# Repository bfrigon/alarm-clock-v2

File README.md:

alarm-clock
===========

3D Model render:

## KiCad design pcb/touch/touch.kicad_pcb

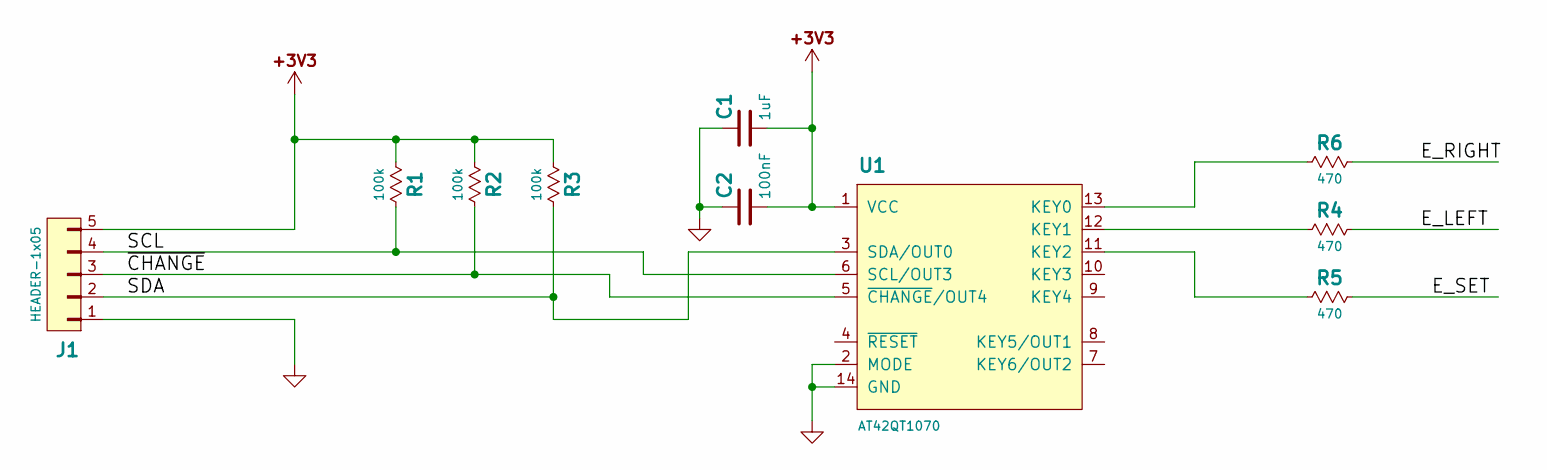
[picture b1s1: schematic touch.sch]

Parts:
C1: 1uF; C-0805
C2: 100nF; C-0603
J1: HEADER-1x05; WP-50mil-1x05
R1, R2, R3: 100k; C-0603
R4, R5, R6: 470; C-0603
U1: AT42QT1070; 14N

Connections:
+3V3: C1.1, C2.1, J1.5, R1.1, R2.1, R3.1, U1.1 (VCC)
/E_LEFT: R4.2
/E_RIGHT: R6.2
/E_SET: R5.2
/SCL: J1.4, R1.2, U1.6 (SCL/OUT3)
/SDA: J1.2, R3.2, U1.3 (SDA/OUT0)
/~CHANGE: J1.3, R2.2, U1.5 (~CHANGE~/OUT4)
GND: C1.2, C2.2, J1.1, U1.2 (MODE), U1.14 (GND)
unnamed: R4.1, U1.12 (KEY1)
unnamed: R5.1, U1.11 (KEY2)
unnamed: R6.1, U1.13 (KEY0)

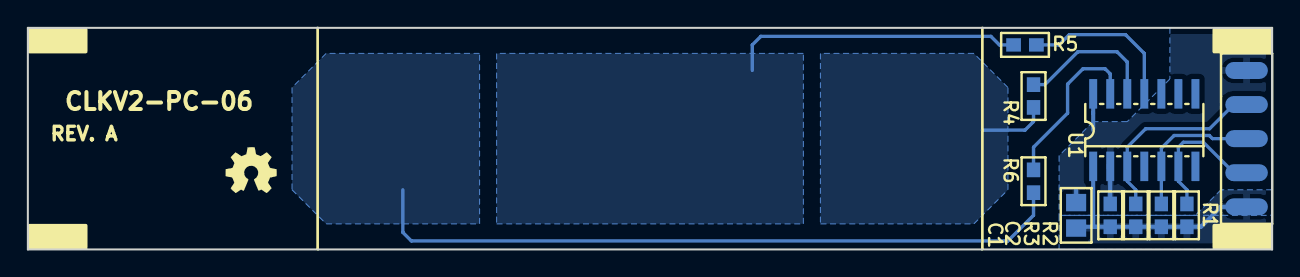
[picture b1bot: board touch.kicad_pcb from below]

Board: 2 copper layers, 92.7 x 16.5 mm, 11 parts (11 on the bottom side), 8 nets.

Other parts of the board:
LOGO-OSHW-150: OSHW; LOGO-OSHW-150

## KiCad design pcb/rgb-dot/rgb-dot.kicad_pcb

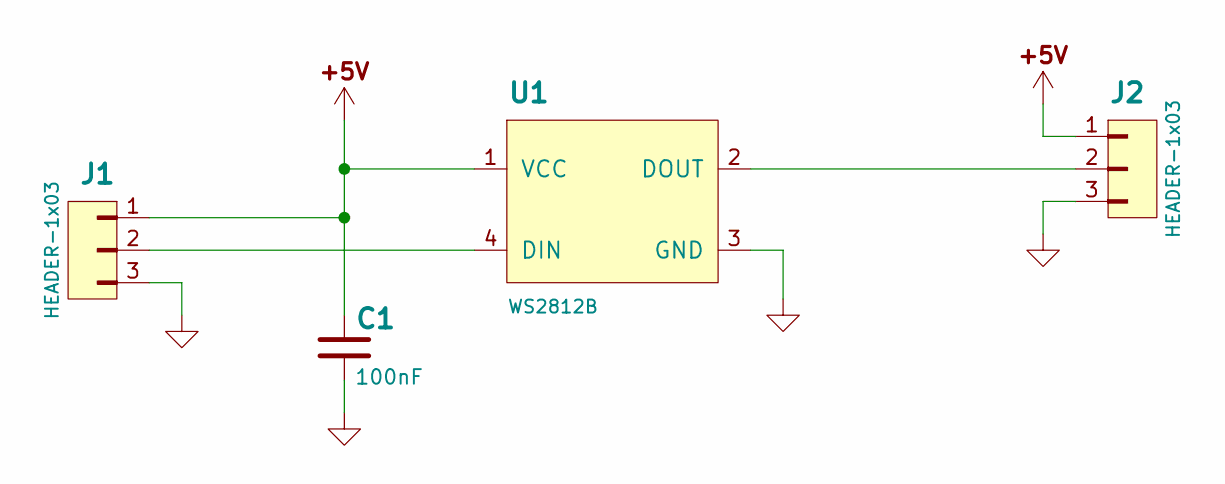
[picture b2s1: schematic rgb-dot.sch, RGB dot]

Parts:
C1: 100nF; C-0603
J1, J2: HEADER-1x03; WP-50mil-1x03
U1: WS2812B; LED-5050

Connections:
+5V: C1.2, J1.1, J2.1, U1.1 (VCC)
/DIN: J1.2, U1.4 (DIN)
/DOUT: J2.2, U1.2 (DOUT)
GND: C1.1, J1.3, J2.3, U1.3 (GND)

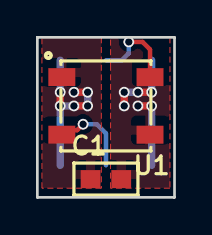
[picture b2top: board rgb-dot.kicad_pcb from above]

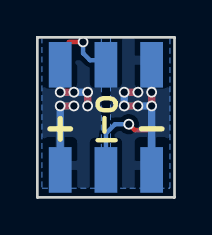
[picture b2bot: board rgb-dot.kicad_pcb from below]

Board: 2 copper layers, 7.6 x 8.9 mm, 4 parts (2 on the bottom side), 4 nets.

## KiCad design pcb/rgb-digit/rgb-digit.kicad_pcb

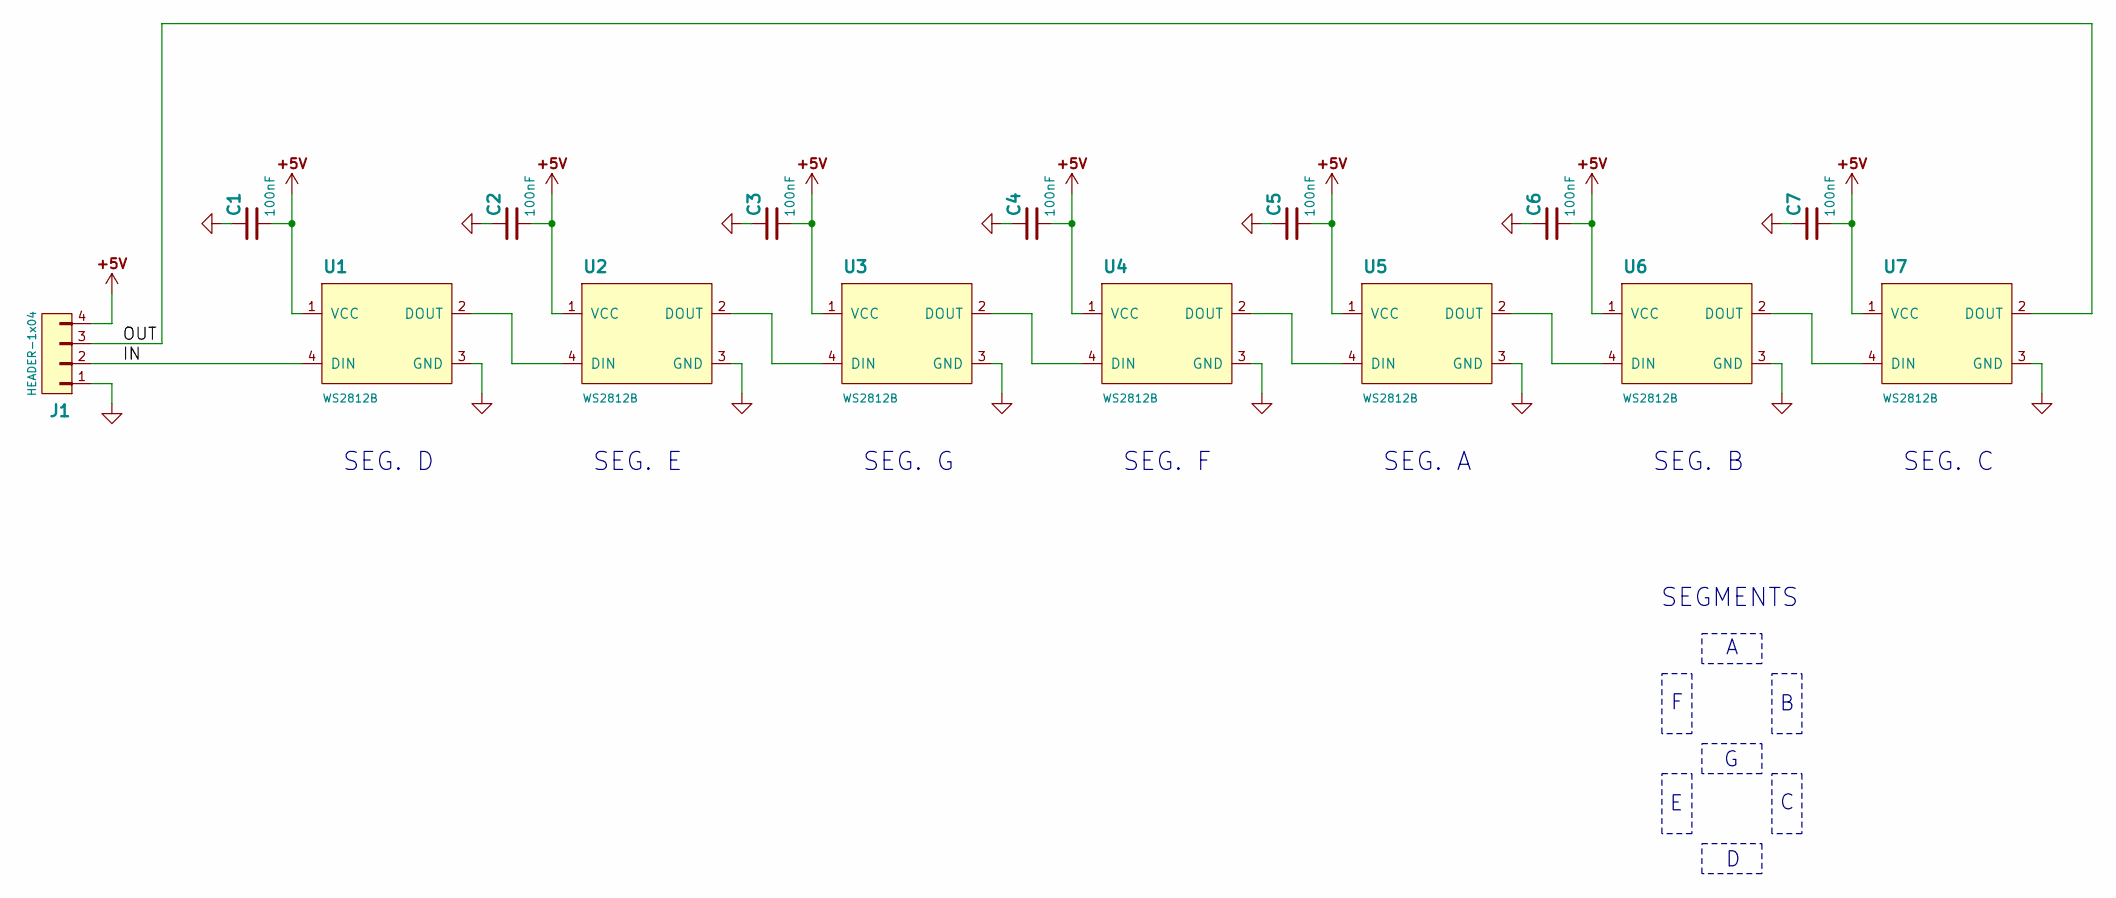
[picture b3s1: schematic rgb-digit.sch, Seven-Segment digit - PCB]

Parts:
C1, C2, C3, C4, C5, C6, C7: 100nF; C-0603
J1: HEADER-1x04; WP-50mil-1x04
U1, U2, U3, U4, U5, U6, U7: WS2812B; LED-5050

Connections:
+5V: C1.1, C2.1, C3.1, C4.1, C5.1, C6.1, C7.1, J1.4, U1.1 (VCC), U2.1 (VCC), U3.1 (VCC), U4.1 (VCC), U5.1 (VCC), U6.1 (VCC), U7.1 (VCC)
/IN: J1.2, U1.4 (DIN)
/OUT: J1.3, U7.2 (DOUT)
GND: C1.2, C2.2, C3.2, C4.2, C5.2, C6.2, C7.2, J1.1, U1.3 (GND), U2.3 (GND), U3.3 (GND), U4.3 (GND), U5.3 (GND), U6.3 (GND), U7.3 (GND)
unnamed: U1.2 (DOUT), U2.4 (DIN)
unnamed: U2.2 (DOUT), U3.4 (DIN)
unnamed: U3.2 (DOUT), U4.4 (DIN)
unnamed: U4.2 (DOUT), U5.4 (DIN)
unnamed: U5.2 (DOUT), U6.4 (DIN)
unnamed: U6.2 (DOUT), U7.4 (DIN)

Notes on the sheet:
SEG. D
SEG. E
SEG. G
SEG. F
SEG. A
SEG. B
SEG. C
SEGMENTS

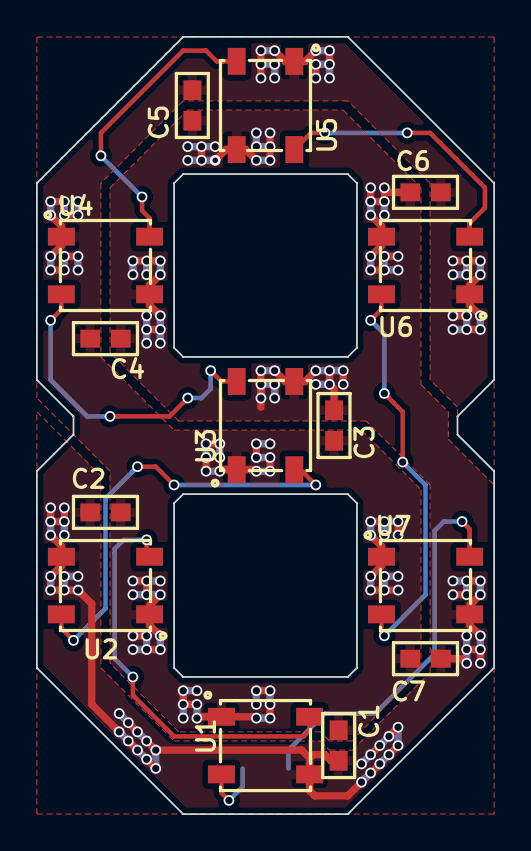
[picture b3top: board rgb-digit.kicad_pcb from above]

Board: 2 copper layers, 25.4 x 43.2 mm, 15 parts (1 on the bottom side), 10 nets.

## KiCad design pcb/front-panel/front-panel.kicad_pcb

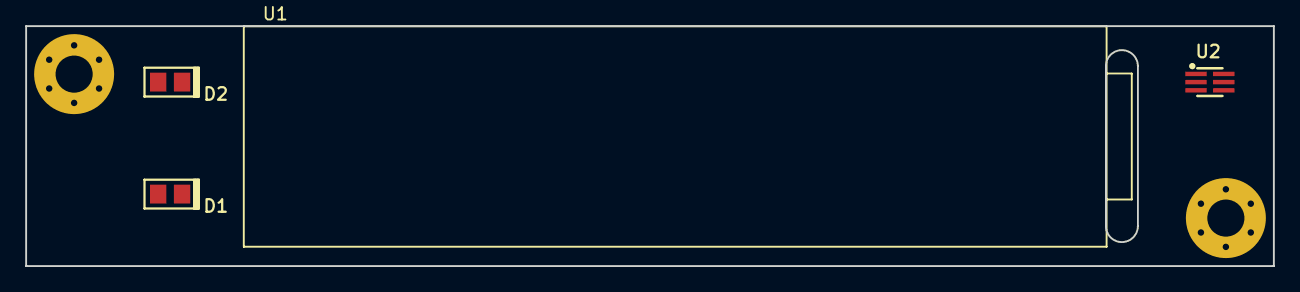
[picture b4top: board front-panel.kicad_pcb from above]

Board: 2 copper layers, 99.1 x 19.0 mm, 7 parts (1 on the bottom side), 4 nets, no tracks yet.

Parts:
D1, D2: LED; LED-0805
J1: HEADER-1x05; WP-50mil-1x05
REF: Hole-Screw-#4
REF#2: Hole-Screw-#4
U1: ER-OLED1602-4W; LCD-ER-OLED1602
U2: TSL2561; 6

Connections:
+3V3: J1.1, U1.6, U1.10
/SCL: J1.3, U1.18
/SDA: J1.2, U1.19, U1.20
GND: J1.5, U1.1, U1.3, U1.9, U1.11, U1.13, U1.16, U1.17, U1.21, U1.22, U1.23, U1.24, U1.25, U1.27, U1.28, U1.29, U1.30, U1.33

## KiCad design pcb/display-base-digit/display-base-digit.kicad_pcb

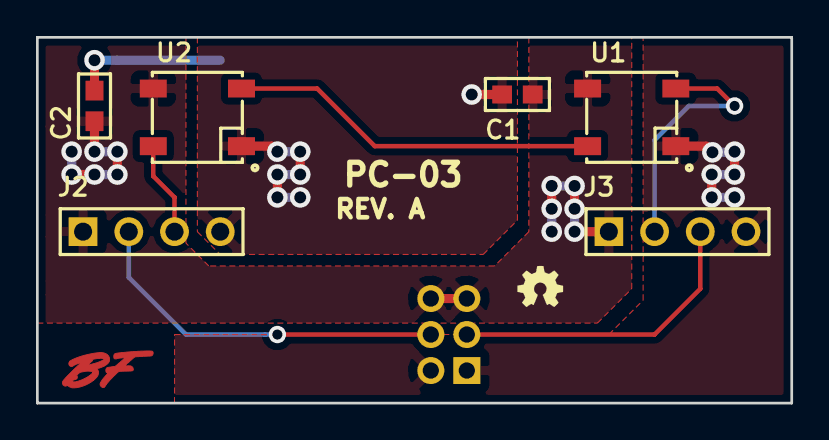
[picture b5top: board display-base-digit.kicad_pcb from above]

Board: 2 copper layers, 41.9 x 20.3 mm, 9 parts (1 on the bottom side), 7 nets.

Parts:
C1, C2: 100nF; C-0603
J1: HEADER-2x03; 2MM-HDR-M-2x03
J2, J3: HEADER-1x04; HDR-M-1x04
LOGO-OSHW-100: OSHW; LOGO-OSHW-100
SIGNATURE: LOGO; SIGNATURE
U1, U2: WS2812B; LED-5050

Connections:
+5V: C1.1, C2.1, J1.5, J1.6, J2.1, J3.1, U1.1, U2.1
/DIN: J1.3, J3.3
/DOUT: J1.4, J2.2
GND: C1.2, C2.2, J1.1, J1.2, J2.4, J3.4, U1.3, U2.3
unnamed: J2.3, U2.2
unnamed: J3.2, U1.4
unnamed: U1.2, U2.4

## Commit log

2015-06-05 Added STL files
2015-09-01 Added STD models
2015-09-01 Updated PCB pc-01 pc-02, Added display base pcb (pc-03, pc-04)
2015-09-01 Added pdf schematics
2015-09-01 Updated gerber files for 0.8mm 5x5 panel
2015-09-01 Added 3D model render
2015-10-22 Update 3D model render
2015-11-04 Added mechanical drawings for RGB 7-segments digit, RGB dots
2015-11-04 Updated schematics
2015-11-04 Updated STL files
2015-11-25 Updated mechanical drawings
2015-11-26 Added CLKV2-DWG-14 drawing (bottom cover)
2015-11-26 Updated directory structure
2015-11-26 Modified keep-out zones
2015-11-26 Added material volume in drawings of 3D printed parts
